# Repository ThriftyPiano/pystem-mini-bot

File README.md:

# PySTEM Mini Bot

## Project Overview

The PySTEM Mini Bot is an open-source educational robotics platform. Created by Rick Zhou and Kevin Zhou, this project provides an affordable alternative to expensive educational robotics kits.

## Core Components
- **Microcontroller**: ESP32 chip with WiFi/bluetooth connectivity
- **Chassis**: 3D-printed design
- **Motors**: Two continuous microservo-powered wheels with encoders
- **Sensors**: IR reflective sensor for line detection and color recognition
- **Power**: 6V battery pack
- **Wiring**: Solderless assembly

## Technical Challenges

### 1. Motor Encoder Noise and Debouncing

The LM393 encoder modules generate 20 pulses per wheel revolution, but in practice the raw signal was noisy — spurious pulses from electrical interference caused the robot to miscount its position, leading to unpredictable movements and overshooting targets.

**Solution:** I implemented a multi-layer debouncing strategy in the encoder interrupt handler. A 5ms time-based filter ignores pulses that arrive faster than physically possible, filtering out electrical noise without losing real data. I also added `Pin.PULL_UP` to stabilize the digital input, and built a separate 200ms debounce for the start button interrupt to prevent false program triggers. Getting the debounce thresholds right required iterative testing on the actual hardware — too aggressive and real pulses get dropped, too lenient and noise slips through.

### 2. Precise Motor Position Control on Low-Cost Hardware

Cheap continuous microservos don't have built-in position feedback. Moving the robot a specific distance (e.g., "drive forward 360 degrees of wheel rotation") required building a closed-loop position controller from scratch using the encoder pulses.

**Solution:** I wrote a proportional controller that runs on a timer interrupt, continuously comparing the target position against the encoder count and adjusting motor power. Key engineering decisions included setting a minimum power threshold (15%) to prevent motor stalling at low speeds, a tolerance band (30 degrees) for "close enough" arrival detection to avoid oscillation, and velocity limiting to prevent overshooting. When the motor needs to hard-stop, the controller cuts the PWM signal entirely rather than sending a neutral pulse — a subtle fix that eliminated drift at rest.

### 3. Uploading Code Over Serial to a Memory-Constrained ESP32

The ESP32 has very limited filesystem space, and sending large Python files over WebSerial would frequently trigger `OSError 28` (filesystem full) or corrupt mid-transfer.

**Solution:** I designed a hex-encoding upload protocol in `robot.js`. Instead of writing the file directly, the browser converts the code to a hex string, splits it into 512-byte chunks, and sends each chunk as a MicroPython command that reconstructs the bytes on-device. The protocol includes explicit garbage collection (`gc.collect()`) between chunks to reclaim memory. This approach also avoids issues with special characters in the code breaking the serial transfer.

### 4. Building a Browser-Based IDE With No Backend

The entire programming environment runs client-side — there's no server processing code. This was a deliberate decision to eliminate setup friction (no installation, no accounts), but it meant solving problems typically handled server-side.

**Solution:** The IDE uses the Monaco Editor (the engine behind VS Code) with custom MicroPython autocomplete generated from `.pyi` stub files I wrote for the ESP32 hardware modules. File management uses `localStorage` for persistence with auto-save. The WebSerial API handles direct USB communication to the robot. I also added a Blockly-based visual programming mode (`scratch.html`) that generates Python code in real time, giving beginners a drag-and-drop entry point while still producing real, readable code.

### 5. Straight-Line Correction With an IMU

Even with matched motors, the robot drifts when driving "straight" due to slight differences in wheel friction and motor response. This is a fundamental problem with differential-drive robots.

**Solution:** I integrated the MPU-6050 accelerometer/gyroscope and wrote an orientation correction loop in the motor pair module. When driving straight, the controller reads the gyroscope heading and applies a steering offset to compensate for drift, keeping the robot on course. This required careful calibration of the sensor and tuning the correction gain to avoid over-correcting.

### 6. SPIKE Prime API Compatibility

I wanted the robot's programming interface to be familiar to students who have used LEGO SPIKE Prime, so they could transfer their skills between platforms.

**Solution:** I implemented a SPIKE Prime-compatible Python API (`sdk_motor.py`, `sdk_motor_pair.py`, etc.) that mirrors the LEGO API's function signatures and behavior. Functions like `motor_pair.move()`, `motor_pair.move_tank()`, and `motor.run_to_position()` work the same way, so example code and curriculum designed for SPIKE Prime can run on this robot with minimal changes — at a fraction of the cost.

## Getting Started

1. Visit [robot.pystem.com](https://robot.pystem.com/)
2. Follow assembly instructions to prepare and assemble your robot
3. Flash firmware following the instructions
4. Start programming with the browser IDE

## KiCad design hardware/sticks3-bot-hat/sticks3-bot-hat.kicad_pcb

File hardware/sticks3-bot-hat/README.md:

# PySTEM Mini Bot — StickS3 HAT

A 48 x 33 mm carrier PCB (4 servo + 4 sensor headers in two rows) that turns an M5StickS3 into the Mini Bot's
brain. The stick plugs into a right-angle HAT2 header and **lies flat** on
the robot (screen up, body overhanging the board edge); everything else is
solderless connectors, so a batch of bots assembles with a screwdriver.

```
4xAA box (6V, own switch) -> 5.5x2.1 barrel jack (center +)
    +-> servo rail (6V, 4x 3-pin headers, bottom row)
    +-> AP63205 buck (5.0V) -> StickS3 5V_IN
StickS3 3V3 -> encoder / color-sensor headers (S3 pins are NOT 5V-tolerant)
    +-> buck 5V -> DIST header (HC-SR04); its 5V ECHO is divided to 3.3V by R4/R5
```

Never feed the 6 V pack into the stick directly: fresh alkalines sit at
6.4 V and the stick's internal power chips are 5 V parts — that's what the
buck (U1 + L1 + C1/C3/C4/C5) is for. C7 (470 uF) rides through servo-stall
sag so the stick doesn't brown out. The IMU is the stick's internal BMI270
(`sticks3.imu()`), so there is no IMU connector; I2C pull-up resistors were
dropped with it.

## Connectors

| Connector | For | Signals |
|-----------|-----|---------|
| J1 (2x8 right-angle) | StickS3 HAT2 socket | all of the below |
| WHEEL A / WHEEL B | continuous-rotation wheel servos | G5 / G4, 6 V rail |
| PAN / TILT | head positional servos | G6 / G7, 6 V rail |
| ENC A / ENC B (1x3: `V G D`) | LM393 photo-interrupter wheel encoders, D0 output | G43 / G44, 3V3 |
| COLOR (1x4: `V G - A`) | TCRT5000 reflection / line sensor module, A0 output | G1 (ADC1), 3V3 |
| DIST (1x4: `5 T E G`) | HC-SR04 ultrasonic distance sensor | TRIG G2, ECHO G8 (via 1k/2k divider), 5 V |
| 6V IN (5.5x2.1 barrel jack, top entry, next to the stick) | 4xAA battery box with barrel plug + switch | center = +6 V |

Sensor header pin order follows the common LM393-based modules (`VCC GND
D0 A0`), so a straight 3- or 4-wire Dupont cable connects the encoder or
reflection module pin-for-pin; the COLOR header's third pin is unconnected
(the module's D0). DIST matches the HC-SR04's own `VCC TRIG ECHO GND`.
The power LED (D1, 22k series resistor) is deliberately dim: it only shows
that the 5 V rail is up.

The stick's own Grove port (G9/G10) stays free — the WonderEcho voice
module plugs in there directly.

### Header rows

With the stick screen up, its socket has the GPIO row (G5 G4 G6 G7 G43 G44
G2 G3) on top and the power row (GND EXT_5V BOOT G1 G8 BAT 3V3 5V_IN)
underneath, GND in the column nearest J1's square pad. A right-angle header
feeds its upper pins from the pad row farther from the board edge (J1's odd
pads), so odd pads carry the GPIOs and even pads the power row. **v3 and v4
boards were built with the rows the other way round** (M5Stack's pinout
table numbers the socket from the power row, which was copied into J1). On
those boards nothing is powered and the buck's 5 V lands on G3. Fix in the
field: 11 female-female Dupont wires from the stick's socket to the J1 pads,
same column, other row (GND→2, 3V3→14, 5V_IN→16, G1→8, G8→10, G5→1, G4→3,
G6→5, G7→7, G43→9, G44→11); tested on a v3 board with all sensors and
servos. v5 swaps the rows in the design (`gen/tools/rework_v5_j1rows.py`).

## GPIO map (for the firmware port)

| Role | GPIO | Notes |
|------|------|-------|
| Servo A (left wheel) | G5 | LEDC PWM, 50 Hz |
| Servo B (right wheel) | G4 | LEDC PWM, 50 Hz |
| Head pan | G6 | LEDC PWM, 50 Hz |
| Head tilt | G7 | LEDC PWM, 50 Hz |
| Encoder A | G43 | input, pull-up (UART0 TX pin — free with native USB) |
| Encoder B | G44 | input, pull-up (UART0 RX pin — free with native USB) |
| Color / reflection sensor (port C) | G1 | ADC1_CH0 |
| Distance sensor TRIG (port D) | G2 | output, 10 us pulse |
| Distance sensor ECHO (port D) | G8 | input, 5 V pulse divided to 3.3 V on the HAT; `machine.time_pulse_us` |
| IMU | internal BMI270 | via `sticks3.imu()` |

## Ordering a batch (JLCPCB)

1. The committed `fab/` outputs (`sticks3-bot-hat-gerbers.zip`, `bom.csv`,
   `positions.csv`) are the v5 exports. To regenerate, run `gen/export.sh`
   (needs KiCad 10) — it refills the zones itself before exporting, since
   `kicad-cli` exports whatever fill is stored in the board file.
2. Upload the gerber zip at jlcpcb.com. 2-layer, 1.6 mm, any color.
3. Enable "PCB Assembly" (economy, top side). Upload `bom.csv` and
   `cpl-jlcpcb-corrected.csv` (not `positions.csv`, see below). Every BOM
   row carries an LCSC number that was matched for the v5 order, so the
   matcher should resolve all of them without a manual search; just check
   nothing shows as out of stock (backups are listed above the `BOM` table
   in `gen/design.py`). Two numbers in older BOMs were wrong: C4190 is 2.2k
   (not 22k) and C4109 is the 0402 2k — R3 is C31850 and R5 is C22975 now.
   `positions.csv` is kicad-cli's raw placement export (KiCad rotations);
   `fab/cpl-jlcpcb-corrected.csv` is the same placement in JLC's column
   format with the part rotations hand-corrected in JLC's preview, and is
   what the boards were built from. `export.sh` regenerates `positions.csv`
   so a moved part shows up as a diff; carry that change into the CPL by
   hand and re-check the rotation in JLC's preview.
   Mounting holes are M3 (3.2 mm); use screws with heads <= 5.5 mm, the
   two left holes sit close to the J1/J2 headers.

## First-article checklist (board #1, before servos)

1. Visual: no bridges around U1/L1.
2. Battery unplugged: no short between servo rail and GND.
3. Battery box plugged in and switched on (stick removed): 5.0 V +-0.1 on
   J1 pin 16 (5V_IN, even row, last column) vs GND, LED faintly lit (it runs at ~0.14 mA on purpose).
   Battery box must be wired center-positive.
   With an HC-SR04 on DIST and a 5 V level on its ECHO pin, J1 pin 10 (G8)
   must read ~3.3 V — that's the R4/R5 divider doing its job.
4. **Orientation check — the HAT2 socket is unkeyed**: plug the stick in
   screen up, power it from USB only, and meter from the stick's USB-C
   shell (GND) to the J1 pads: pin 2 (the round pad beside the square
   pin 1) must read 0 V and pin 14 (same row, seventh column) 3.3 V. If
   those voltages show up on the square-pad row instead, the header rows
   are swapped (the v3/v4 boards) — see "Header rows" below. Never power
   the battery box with the stick plugged in until this check passes: a
   mis-seated stick gets the buck's 5 V on a GPIO or on its GND.
5. The stick cantilevers off the board edge on the header — support its far
   end with a foam pad or standoff on the chassis.

## Design sources

Everything is generated from `gen/design.py` (single source of truth for
connectivity) by `gen/gen_pcb.py` (board via KiCad's pcbnew API +
freerouting) and `gen/gen_sch.py` (schematic). The routed board was then
hand-finished, so later revisions edit `sticks3-bot-hat.kicad_pcb` in place
(`gen/tools/rework_v4.py` is the scripted v3 -> v4 edit, run in the KiCad
docker image; `gen/tools/rework_v5_j1rows.py` is the v4 -> v5 J1 row swap,
plain text edit, no pcbnew needed) rather than regenerating it. `gen/export.sh` runs ERC/DRC and writes the fab outputs; it
uses `kicad-cli` if installed, otherwise the `kicad/kicad:10.0` docker
image. DRC is clean apart from two courtyard warnings where the M3 holes'
screw-head circle grazes J1/J2.

- `sticks3-bot-hat.kicad_pcb` — routed 2-layer board, 48 x 33 mm, GND pours
- `sticks3-bot-hat.kicad_sch` / `sticks3-bot-hat-schematic.pdf`
- `sticks3-bot-hat.pretty/` — local footprint for the SS12D10 switch
- `render-top.png`, `render-bottom.png`, `render-3d.png` (regenerate with `gen/render.sh`)

### Finishing v5 — done

The v5 row swap was made without KiCad (text edits, `gen/tools/rework_v5_j1rows.py`);
the finishing pass was run with KiCad 10.0.6 on the Mac: zones refilled and
saved into the board file, DRC clean apart from the two known M3 courtyard
grazes, ERC clean, `fab/` regenerated by `gen/export.sh` and the render PNGs
refreshed by `gen/render.sh` (on macOS pass
`KICAD_3DMODELS=~/Applications/KiCad/KiCad.app/Contents/SharedSupport/3dmodels`).
v5 is ready to order at JLCPCB per "Ordering a batch";
`fab/cpl-jlcpcb-corrected.csv` is unchanged (no part moved in v5).

HAT2 pinout reference: [M5Stack StickS3 docs](https://docs.m5stack.com/en/core/StickS3).

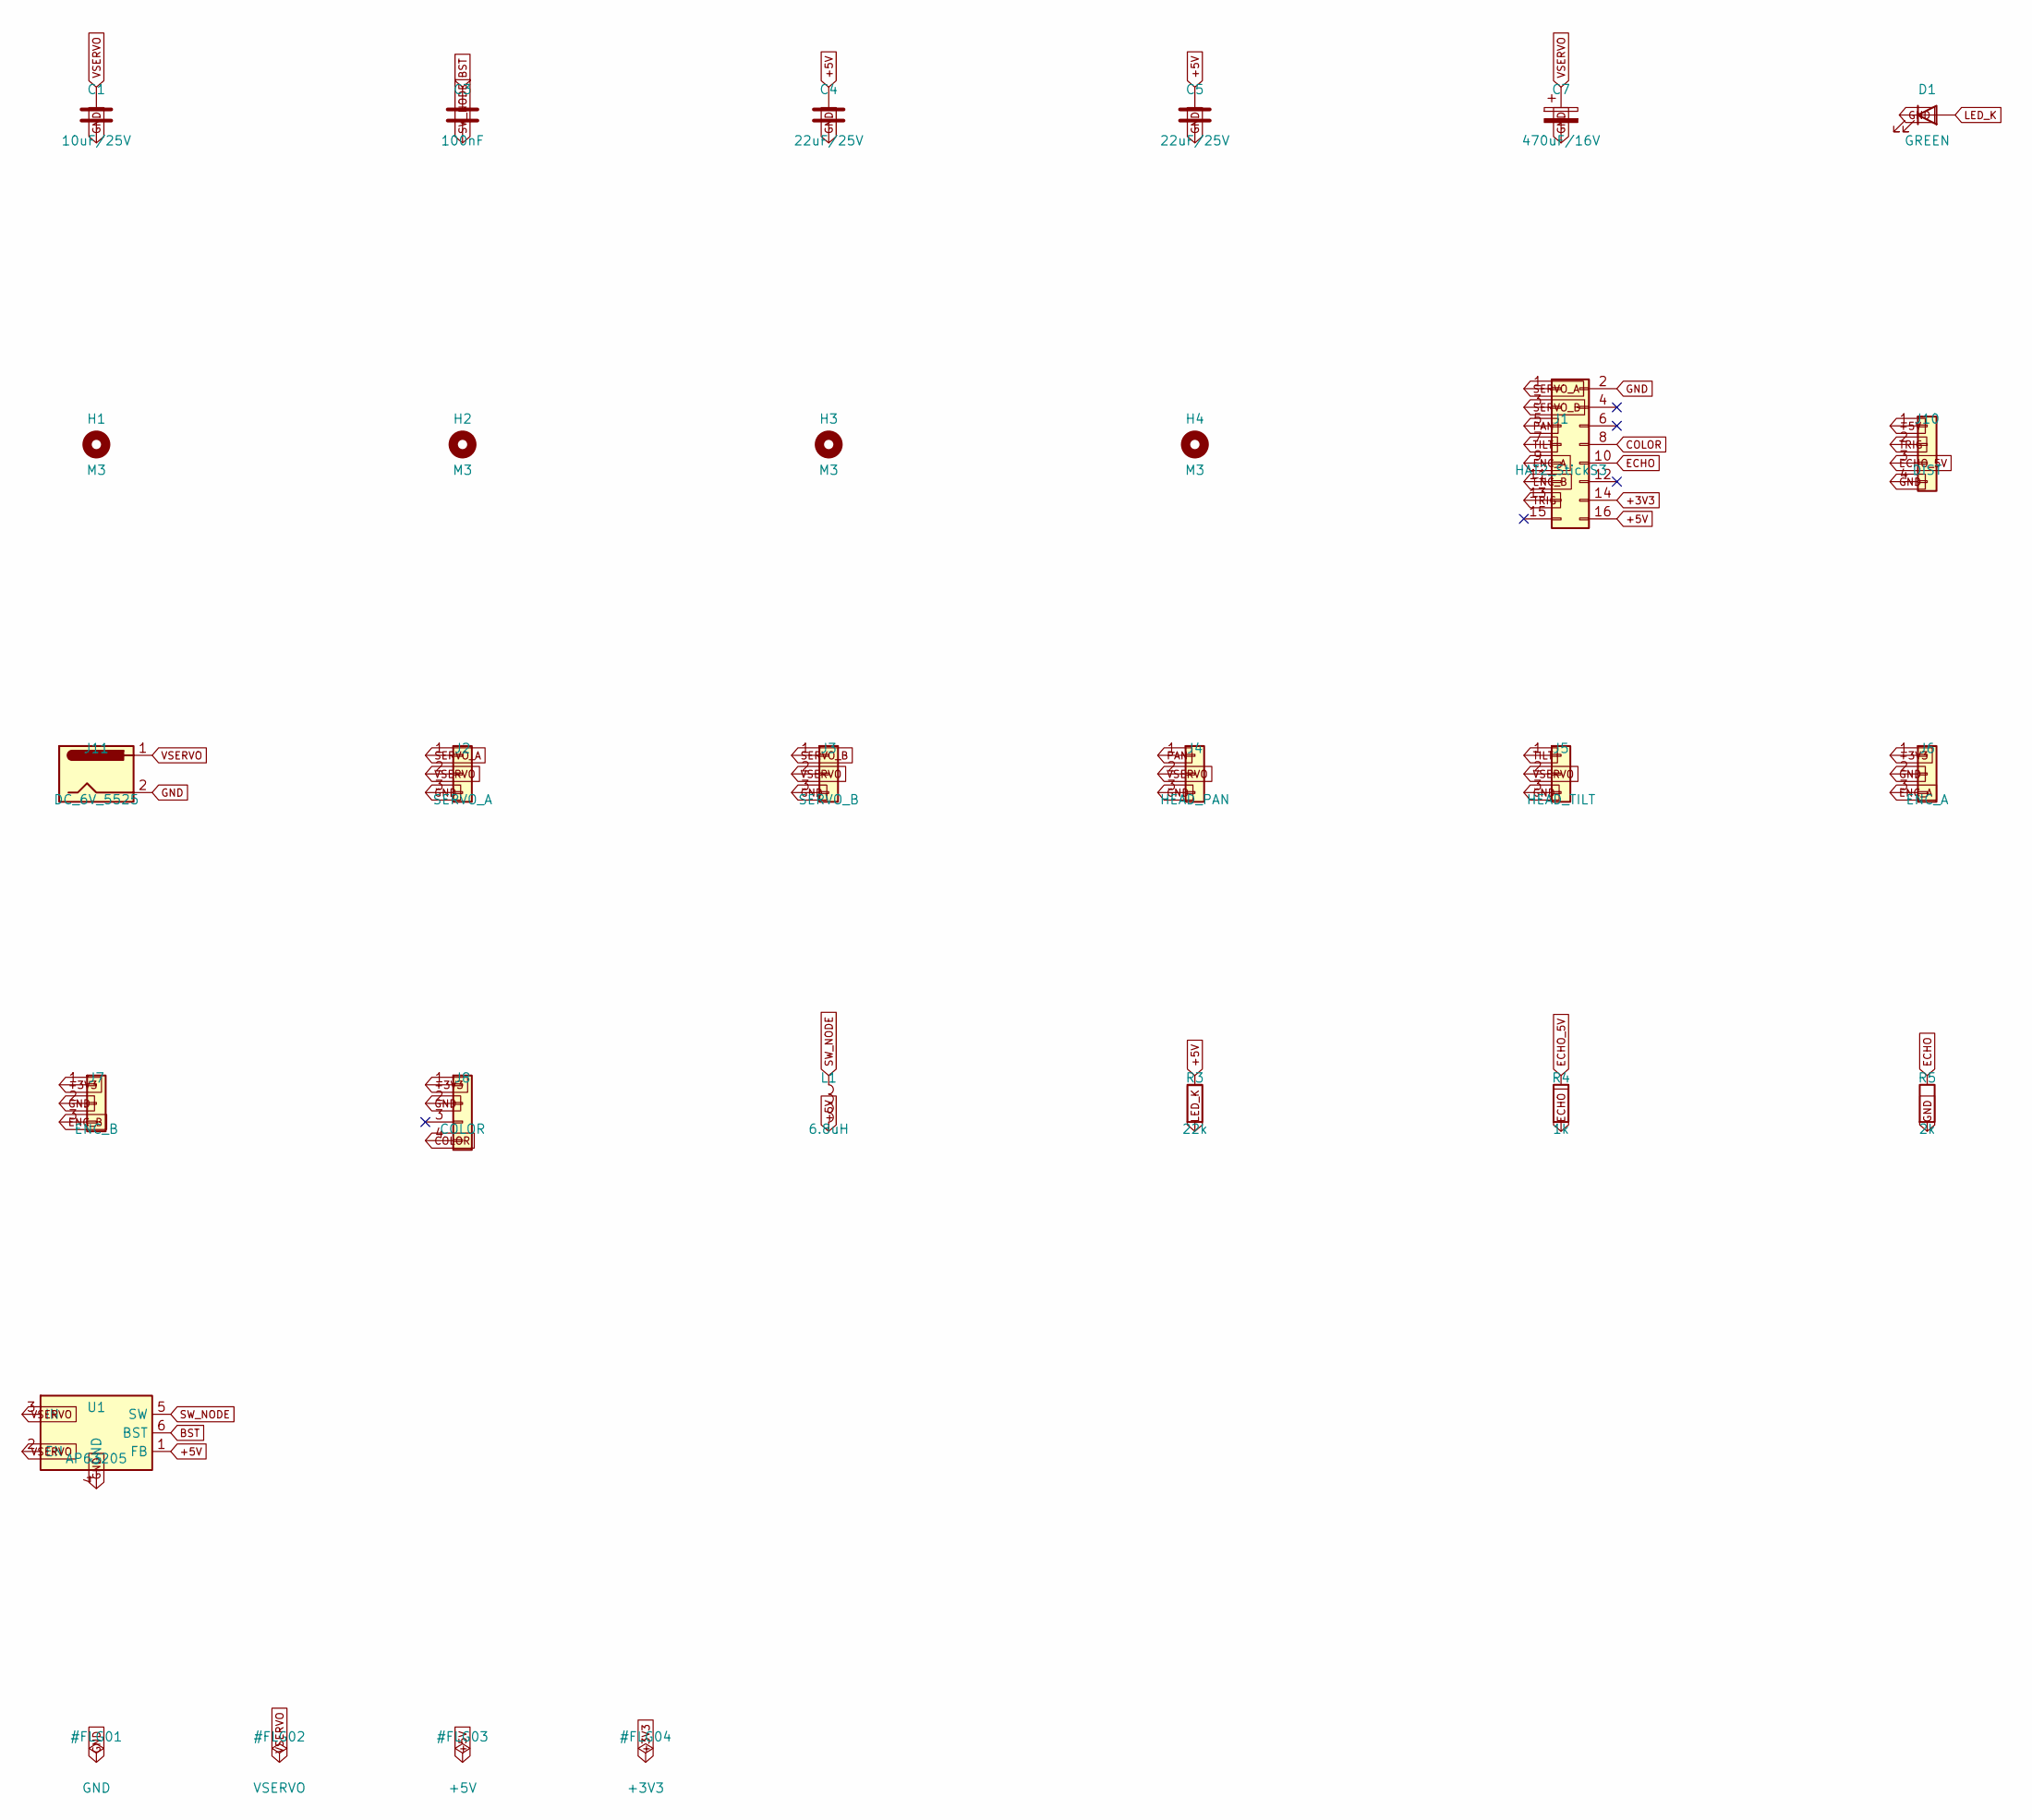
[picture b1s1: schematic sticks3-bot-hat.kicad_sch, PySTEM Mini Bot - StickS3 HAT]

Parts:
C1: 10uF/25V; C_0805_2012Metric
C3: 100nF; C_0603_1608Metric
C4, C5: 22uF/25V; C_1206_3216Metric
C7: 470uF/16V; CP_Radial_D8.0mm_P3.50mm
D1: GREEN; LED_0603_1608Metric
H1, H2, H3, H4: M3; MountingHole_3.2mm_M3
J1: HAT2_StickS3; PinHeader_2x08_P2.54mm_Horizontal
J2: SERVO_A; PinHeader_1x03_P2.54mm_Vertical
J3: SERVO_B; PinHeader_1x03_P2.54mm_Vertical
J4: HEAD_PAN; PinHeader_1x03_P2.54mm_Vertical
J5: HEAD_TILT; PinHeader_1x03_P2.54mm_Vertical
J6: ENC_A; PinHeader_1x03_P2.54mm_Vertical
J7: ENC_B; PinHeader_1x03_P2.54mm_Vertical
J8: COLOR; PinHeader_1x04_P2.54mm_Vertical
J10: DIST; PinHeader_1x04_P2.54mm_Vertical
J11: DC_6V_5525; BarrelJack_Horizontal
L1: 6.8uH; L_Bourns_SRN6045TA
R3: 22k; R_0603_1608Metric
R4: 1k; R_0603_1608Metric
R5: 2k; R_0603_1608Metric
U1: AP63205; TSOT-23-6

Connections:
+3V3: J1.14, J6.1, J7.1, J8.1
+5V: C4.1, C5.1, J1.16, J10.1, L1.2, R3.1, U1.1 (FB)
BST: C3.1, U1.6 (BST)
COLOR: J1.8, J8.4
ECHO: J1.10, R4.2, R5.1
ECHO_5V: J10.3, R4.1
ENC_A: J1.9, J6.3
ENC_B: J1.11, J7.3
GND: C1.2, C4.2, C5.2, C7.2, D1.1 (K), J1.2, J2.3, J3.3, J4.3, J5.3, J6.2, J7.2, J8.2, J10.4, J11.2, R5.2, U1.4 (GND)
LED_K: D1.2 (A), R3.2
PAN: J1.5, J4.1
SERVO_A: J1.1, J2.1
SERVO_B: J1.3, J3.1
SW_NODE: C3.2, L1.1, U1.5 (SW)
TILT: J1.7, J5.1
TRIG: J1.13, J10.2
VSERVO: C1.1, C7.1, J2.2, J3.2, J4.2, J5.2, J11.1, U1.2 (EN), U1.3 (IN)

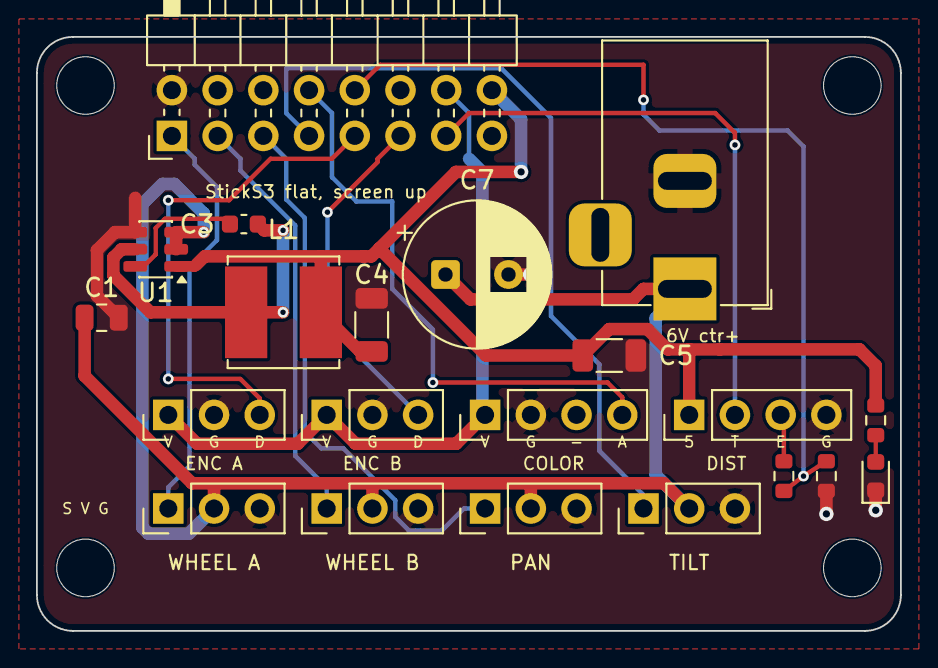
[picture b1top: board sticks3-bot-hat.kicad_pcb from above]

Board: 2 copper layers, 48.0 x 33.0 mm, 25 parts (0 on the bottom side), 17 nets.

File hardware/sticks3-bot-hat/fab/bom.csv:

Designator,Part,Manufacturer,Package,LCSC,Note
U1,AP63205WU-7,Diodes Inc,TSOT-23-6,C2071056,"3.8-32V in, 5V/2A sync buck"
L1,SWPA6045S6R8MT,Sunlord,6045,C57254,6.8uH 3A power inductor
C1,CL21A106KAYNNNE,Samsung,0805,C15850,10uF 25V X5R
C3,CL10B104KB8NNNC,Samsung,0603,C1591,100nF 50V X7R
"C4,C5",CL31A226KAHNNNE,Samsung,1206,C12891,22uF 25V X5R
C7,470uF 16V radial D8xH11.5 P3.5,generic,THT,,bulk for servo stalls
R3,0603WAF2202T5E,UniOhm,0603,C4190,22k 1% (~0.14 mA: dim power LED)
R4,0603WAF1001T5E,UniOhm,0603,C21190,"1k 1% (HC-SR04 ECHO divider, series)"
R5,0603WAF2001T5E,UniOhm,0603,C4109,"2k 1% (HC-SR04 ECHO divider, to GND)"
D1,0603 green LED,generic,0603,,power indicator
J1,2x8 pin header 2.54mm male RIGHT-ANGLE (90 deg),generic,THT,,"plugs into StickS3 HAT2 socket, stick lies flat"
"J2,J3,J4,J5,J6,J7",1x3 pin header 2.54mm male vertical,generic,THT,,servo / encoder headers
"J8,J10",1x4 pin header 2.54mm male vertical,generic,THT,,COLOR (V G - A0) / DIST (HC-SR04) headers
J11,DC barrel jack 5.5x2.1 horizontal (PJ-102A type),generic,THT,,"battery box plugs in, center = +6V"

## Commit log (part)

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2025-08-13 move code to github
2025-08-13 Create CNAME
2025-09-01 Rename index.html to ide.html
2025-09-01 add main page
2025-09-04 add link to thingiverse
2025-09-07 add assembly inst page
2025-09-17 add google analytics tag
2025-09-17 track thingiverse clicks
2025-09-19 name change; gtag for github; add link + image
2025-09-20 add readme; name update
2025-09-21 added assemply instructions
2025-09-21 added discord join button
2025-10-02 add nav bar, comments to code, firmware page
2025-10-04 add discord link, fix nav bar
2025-10-12 upgraded directions
2025-10-31 updated index.html
2026-01-27 fixed motor encoder accuracy
2026-01-27 fixed encoder accuracy
2026-03-12 add Scratch block coding IDE with Blockly
2026-03-12 trigger GitHub Pages deployment
2026-03-14 Add GitHub and STEM Bridge Center links to homepage
2026-03-22 Edit README
2026-05-04 Add CLAUDE.md with repo architecture notes
2026-05-04 Add WonderEcho voice module SDK and voice_drive example
    - examples/sdk_wonder_echo.py: driver for the Hiwonder WonderEcho
    voice recognition + TTS module on I2C 0x34 (read register 0x64
    for recognized command id; write [type, id] to 0x6E to speak).
    - examples/voice_drive.py: beginner-oriented example that polls
    the recognizer and dispatches forward/backward/left/right/stop
    voice commands to motor_pair.
2026-05-05 Strengthen IMU yaw correction and add device test utilities
    Bumps motor_pair straight-line correction gain from kp=10 (clamp ±50) to
    kp=25 (clamp ±150). Diagnostic on hardware showed the old gains saturated
    within 200ms and left a steady ~14° clockwise drift over 720° of travel
    because the correction's ±9% PWM swing couldn't overcome ~17% mechanical
    asymmetry between motors. New gains close the loop to <1° drift.
    Adds util/ with reusable raw-REPL + hex-chunked upload helpers and two
2026-05-05 Add .gitignore and remove accidentally-committed __pycache__
2026-05-05 Stream upload chunks directly to file to avoid ESP32 OOM
    The previous version concatenated all decoded bytes into a single buf
    before f.write(), which silently failed with MemoryError on files >~12KB
    (ESP32 heap can't hold the file plus its hex string contiguously). The
    old upload would error out and leave the prior file in place — easy to
    miss because the device kept booting fine on the stale copy. Now we
    open the file once and write each chunk as it arrives, with a gc.collect
2026-05-05 Add closed-loop velocity control and fix encoder PPR
    Three coupled fixes for straight-line drive:
    1. Encoder PPR was 20 (slot count on the encoder disc) but the disc sits
    on the motor shaft, before a ~2:1 gearbox. So motor.position was
    reporting motor-shaft degrees, not wheel degrees, and every distance
    API was off by ~2x. Bumped to 40 to match what move_for_degrees etc.
    actually mean to a student.
2026-05-05 Make voice_drive continuous and fix stale velocity after motor.stop
    voice_drive previously dispatched each command through
    motor_pair.move_for_degrees(720, ...), which has two problems:
    - Forward/turn commands ran for a fixed ~2s and then auto-stopped,
    instead of running until the next voice command.
    - move_for_degrees with a negative degree target (used for backward)
    is broken: it always starts the motors with positive-direction
2026-05-05 Add slew-limited target and faster integrator for voice-paced turning
    Two coupled changes so voice commands can drive a slow, friction-
    adapting turn:
    motor.py: the velocity controller now tracks a slew-limited
    '_ramped_target' rather than the raw target, so a step command from 0
    to N gets paced at 300 dps/sec. Both wheels accelerate together
    through the soft-start, instead of the stronger motor running ahead
2026-05-07 Slim motor config to A+B and auto-init pins at import
    The robot only has two motors connected. Trimmed MOTOR_PINS to A and
    B, and remapped B from the old (servo=17, encoder=14) pair to the
    current wiring (servo=18, encoder=25). A=left, B=right matches the
    convention motor_pair and voice_drive expect.
    Also init each configured motor at module-import time so every PWM
    pin is explicitly held stopped (duty 0). Without this, a motor whose
2026-05-07 Move start button to GPIO 27, bump voice_drive speeds 1.5x, add startup chime
    - boot.py: BUTTON_PIN 26 -> 27 to give the user more spacing between
    plug headers on the rewired bot.
    - voice_drive.py: DRIVE_VELOCITY 180 -> 270 and TURN_VELOCITY 25 -> 38
    for a livelier feel after the wheel-friction fix; full spin now
    ~10 s instead of ~16 s. Also play TYPE_BROADCAST id=6
    ("parking completed") right after init so it's audible that
